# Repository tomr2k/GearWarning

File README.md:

# (Experimental) Gear Warning System
## Description:
My mechanical limit-switch based gear warning gave me a bit of grief at the start of the soaring season this year.  During winter maintenance I moved both the spoiler and gear position switches but failed to reposition them properly.  Consequently, on the first flight of the season I had to jam a pen into the spoiler's limit switch to get it to stop annoying me!  Perhaps I should have just flown with the gear down ... it wasn't going to be a serious cross-country flight anyway.
So pretty typical of me I decided that in addition to spending five minutes repositioning my spoiler's limit switch, why not spend about that many hours converting the gear warning system to a reed-switch based one!  It's only a matter of time and money and having neither makes this an ideal project.
And now to share my grief, let me make available the design components you will need to make one of your own.  Well, you will still need the buzzer itself, wiring, and most importantly, the magnet attached somewhere to your spoiler and gear handles.  In my case this was accomplished by embedding a magnet in 3d-printed brackets attached to these handles.  Pretty clean, if I say so myself though I have every confidence you can do better!
So here's what you will find in this repository:
- a KiCad-based project for the reed-switched based design: the spoiler and gear warning PCBs are very similar, differing only in the type of reed switch (NO vrs NC) and an additional connector on the GearWarning board to daisy chain the logic.
- gerbers for the PCBs: though you can order these boards directly from OshPark for $2.45/$1.50 (at the time of this writting).  Browse to their [sharing link](https://oshpark.com/shared_projects) and search for GearWarning and SpoilerWarning.
- a [digikey.com](https://www.digikey.com/short/jb349drd) parts list sufficient for building out these boards.

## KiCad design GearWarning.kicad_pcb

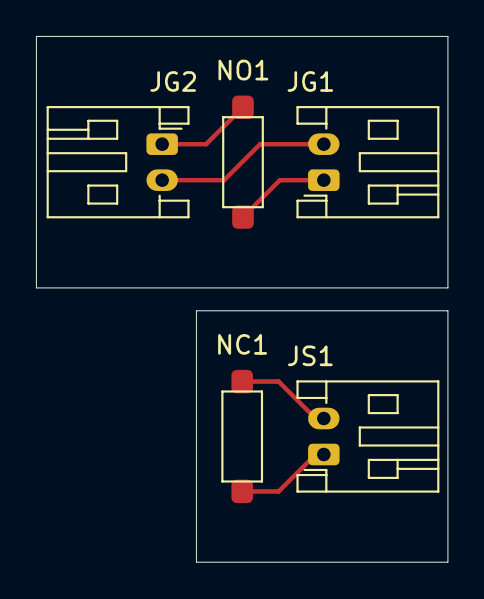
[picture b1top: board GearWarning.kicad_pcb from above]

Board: 2 copper layers, 22.9 x 29.2 mm, 5 parts (0 on the bottom side), 5 nets.

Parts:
JG1: C1; JST_PH_S2B-PH-K_1x02_P2.00mm_Horizontal
JG2: C2; JST_PH_S2B-PH-K_1x02_P2.00mm_Horizontal
JS1: IN; JST_PH_S2B-PH-K_1x02_P2.00mm_Horizontal
NC1: MK24-D-3; MK24-D-2
NO1: MK24-B-3-OE; MK24-D-2

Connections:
unnamed: JG2.1, NO1.2
unnamed: JG1.2, JG2.2
unnamed: JS1.1, NC1.1
unnamed: JS1.2, NC1.2
unnamed: JG1.1, NO1.1

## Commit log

2022-09-23 project update
2022-09-23 initial KiCad release
2022-09-23 initial release of reed switch components
2022-09-24 added circuit diagram to schematic
